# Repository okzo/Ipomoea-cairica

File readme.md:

# Ipomoea-cairica

60% JP or US Keyboard

このキーボードは組み立て時に日本語かUS配列を選択できます。

## JP

## US

## 組み立て方

[こちら](build_guide/build_guide.md)

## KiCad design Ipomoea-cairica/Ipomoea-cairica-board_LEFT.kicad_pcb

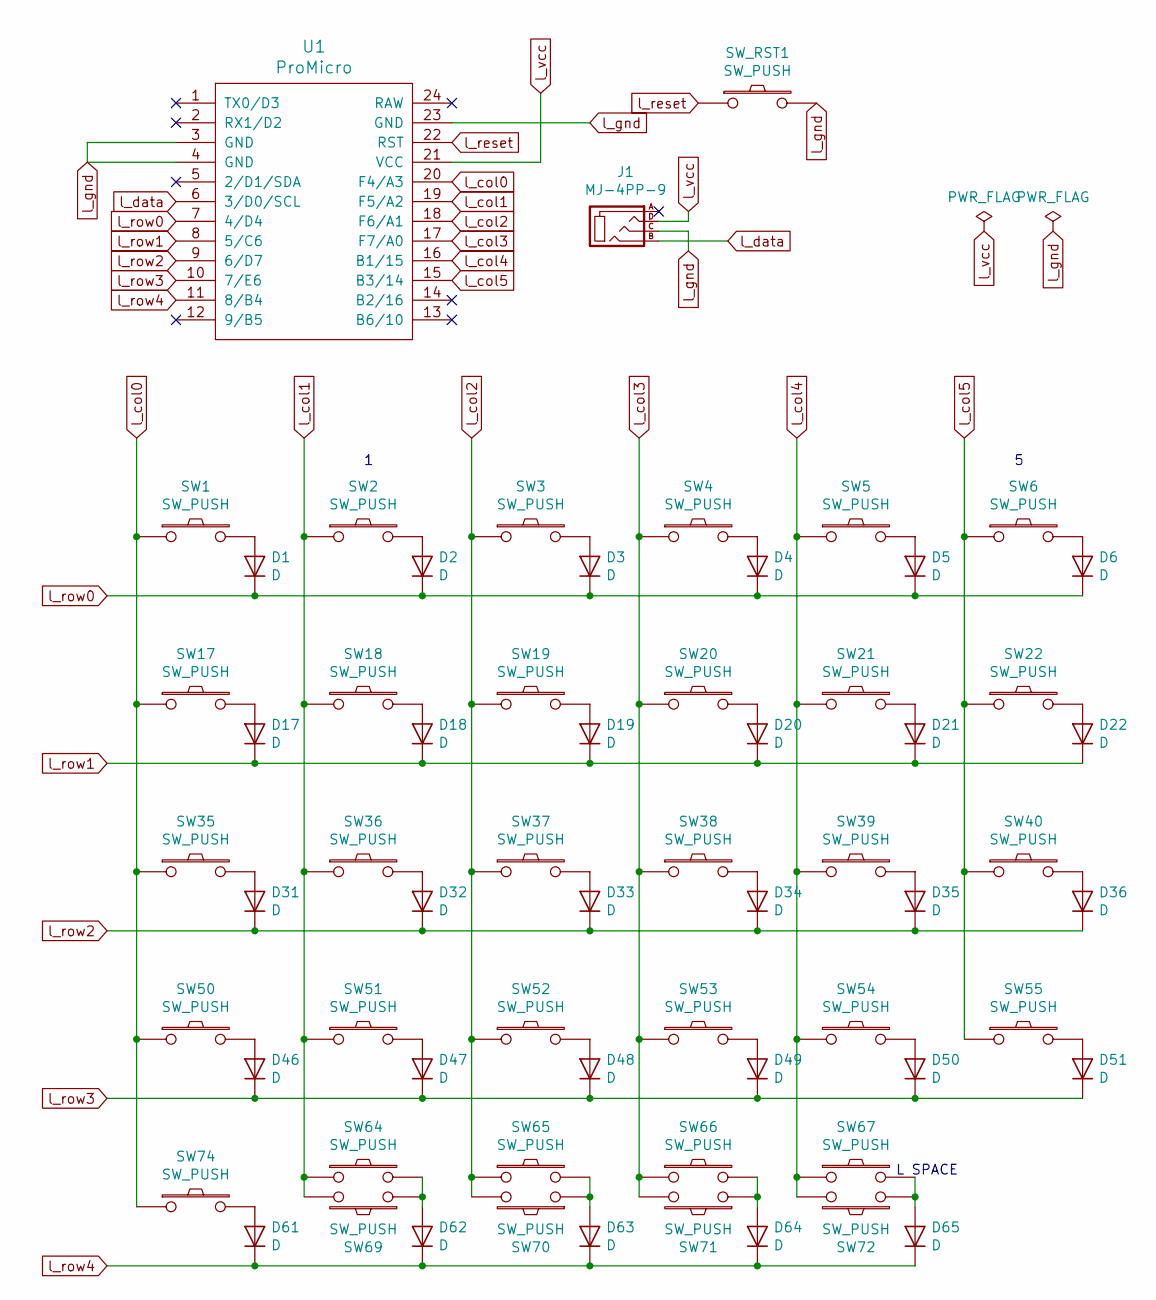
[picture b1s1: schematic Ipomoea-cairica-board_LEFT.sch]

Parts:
D1, D2, D3, D4, D5, D6, D17, D18, D19, D20, D21, D22, D31, D32, D33, D34, D35, D36, D46, D47, D48, D49, D50, D51, D61, D62, D63, D64, D65: D; D3_TH_SMD
J1: MJ-4PP-9; MJ-4PP-9_1side
SW1, SW2, SW3: SW_PUSH; CherryMX-Hotswap_1u_ProMicro
SW4: SW_PUSH; CherryMX-Hotswap_1u_TRRS
SW5, SW6, SW18, SW19, SW20, SW21, SW22, SW36, SW37, SW38, SW39, SW40, SW51, SW52, SW53, SW54, SW55, SW64, SW66: SW_PUSH; CherryMX-Hotswap_1u
SW17: SW_PUSH; CherryMX-Hotswap_1.5u
SW35, SW67: SW_PUSH; CherryMX-Hotswap_1.75u
SW50: SW_PUSH; CherryMX-Hotswap_2.25u
SW65, SW69, SW70, SW71, SW72, SW74: SW_PUSH; CherryMX-Hotswap_1.25u
SW_RST1: SW_PUSH; ResetSW_1side
U1: ProMicro

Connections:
unnamed: D1.2 (A), SW1.2
unnamed: D2.2 (A), SW2.2
unnamed: D3.2 (A), SW3.2
unnamed: D4.2 (A), SW4.2
unnamed: D5.2 (A), SW5.2
unnamed: D6.2 (A), SW6.2
unnamed: D17.2 (A), SW17.2
unnamed: D18.2 (A), SW18.2
unnamed: D19.2 (A), SW19.2
unnamed: D20.2 (A), SW20.2
unnamed: D21.2 (A), SW21.2
unnamed: D22.2 (A), SW22.2
unnamed: D31.2 (A), SW35.2
unnamed: D32.2 (A), SW36.2
unnamed: D33.2 (A), SW37.2
unnamed: D34.2 (A), SW38.2
unnamed: D35.2 (A), SW39.2
unnamed: D36.2 (A), SW40.2
unnamed: D46.2 (A), SW50.2
unnamed: D47.2 (A), SW51.2
unnamed: D48.2 (A), SW52.2
unnamed: D49.2 (A), SW53.2
unnamed: D50.2 (A), SW54.2
unnamed: D51.2 (A), SW55.2
unnamed: D61.2 (A), SW74.2
unnamed: D62.2 (A), SW64.2, SW69.1
unnamed: D63.2 (A), SW65.2, SW70.1
unnamed: D64.2 (A), SW66.2, SW71.1
unnamed: D65.2 (A), SW67.2, SW72.1
l_col0: SW1.1, SW17.1, SW35.1, SW50.1, SW74.1, U1.20 (F4/A3)
l_col1: SW2.1, SW18.1, SW36.1, SW51.1, SW64.1, SW69.2, U1.19 (F5/A2)
l_col2: SW3.1, SW19.1, SW37.1, SW52.1, SW65.1, SW70.2, U1.18 (F6/A1)
l_col3: SW4.1, SW20.1, SW38.1, SW53.1, SW66.1, SW71.2, U1.17 (F7/A0)
l_col4: SW5.1, SW21.1, SW39.1, SW54.1, SW67.1, SW72.2, U1.16 (B1/15)
l_col5: SW6.1, SW22.1, SW40.1, SW55.1, U1.15 (B3/14)
l_data: J1.B, U1.6 (3/D0/SCL)
l_gnd: J1.C, SW_RST1.2, U1.3 (GND), U1.4 (GND), U1.23 (GND)
l_reset: SW_RST1.1, U1.22 (RST)
l_row0: D1.1 (K), D2.1 (K), D3.1 (K), D4.1 (K), D5.1 (K), D6.1 (K), U1.7 (4/D4)
l_row1: D17.1 (K), D18.1 (K), D19.1 (K), D20.1 (K), D21.1 (K), D22.1 (K), U1.8 (5/C6)
l_row2: D31.1 (K), D32.1 (K), D33.1 (K), D34.1 (K), D35.1 (K), D36.1 (K), U1.9 (6/D7)
l_row3: D46.1 (K), D47.1 (K), D48.1 (K), D49.1 (K), D50.1 (K), D51.1 (K), U1.10 (7/E6)
l_row4: D61.1 (K), D62.1 (K), D63.1 (K), D64.1 (K), D65.1 (K), U1.11 (8/B4)
l_vcc: J1.D, U1.21 (VCC)

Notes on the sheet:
L SPACE

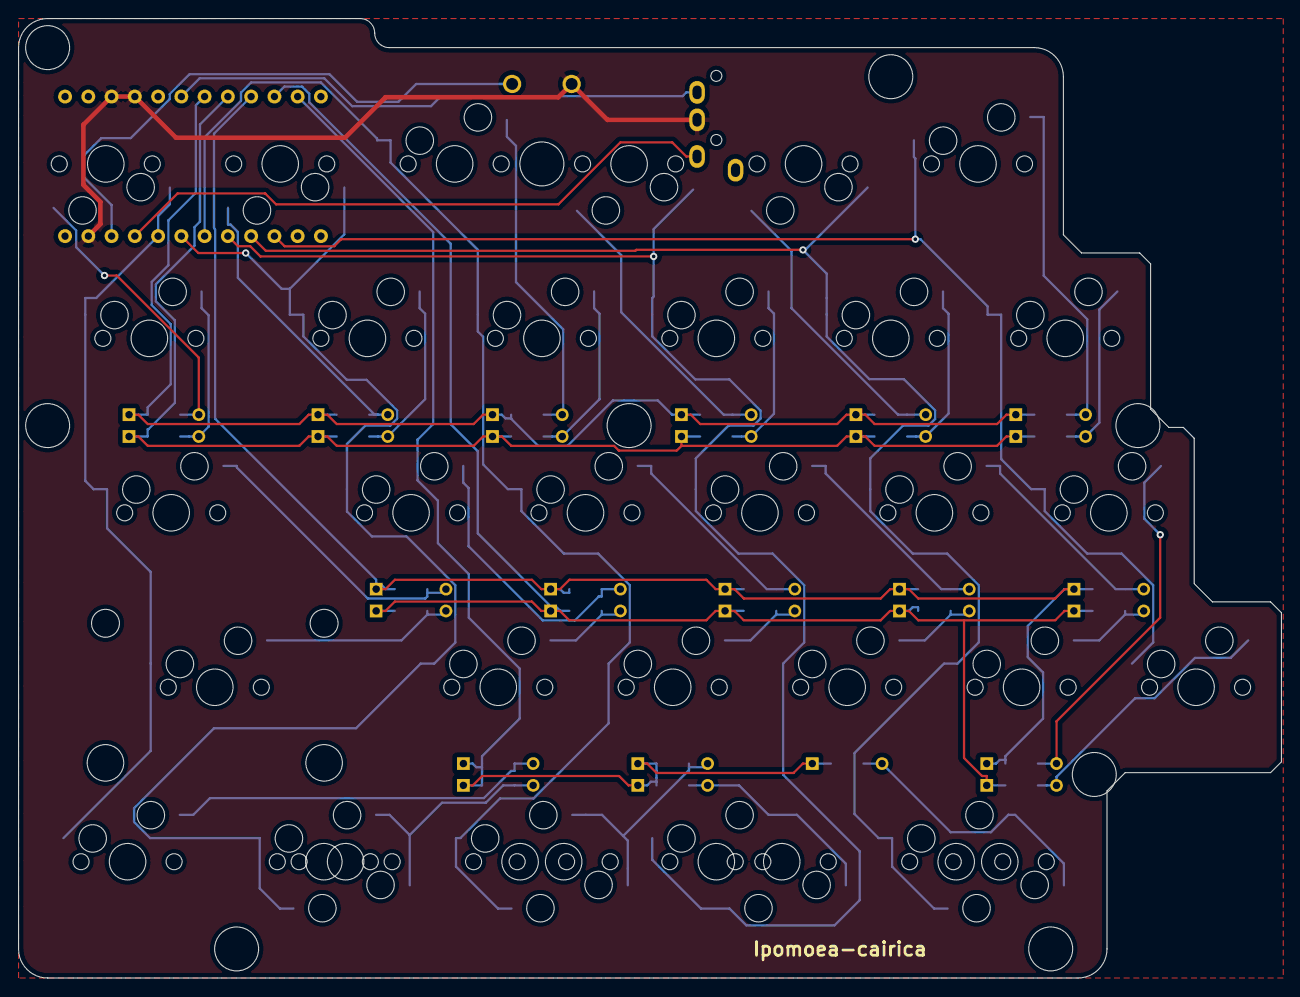
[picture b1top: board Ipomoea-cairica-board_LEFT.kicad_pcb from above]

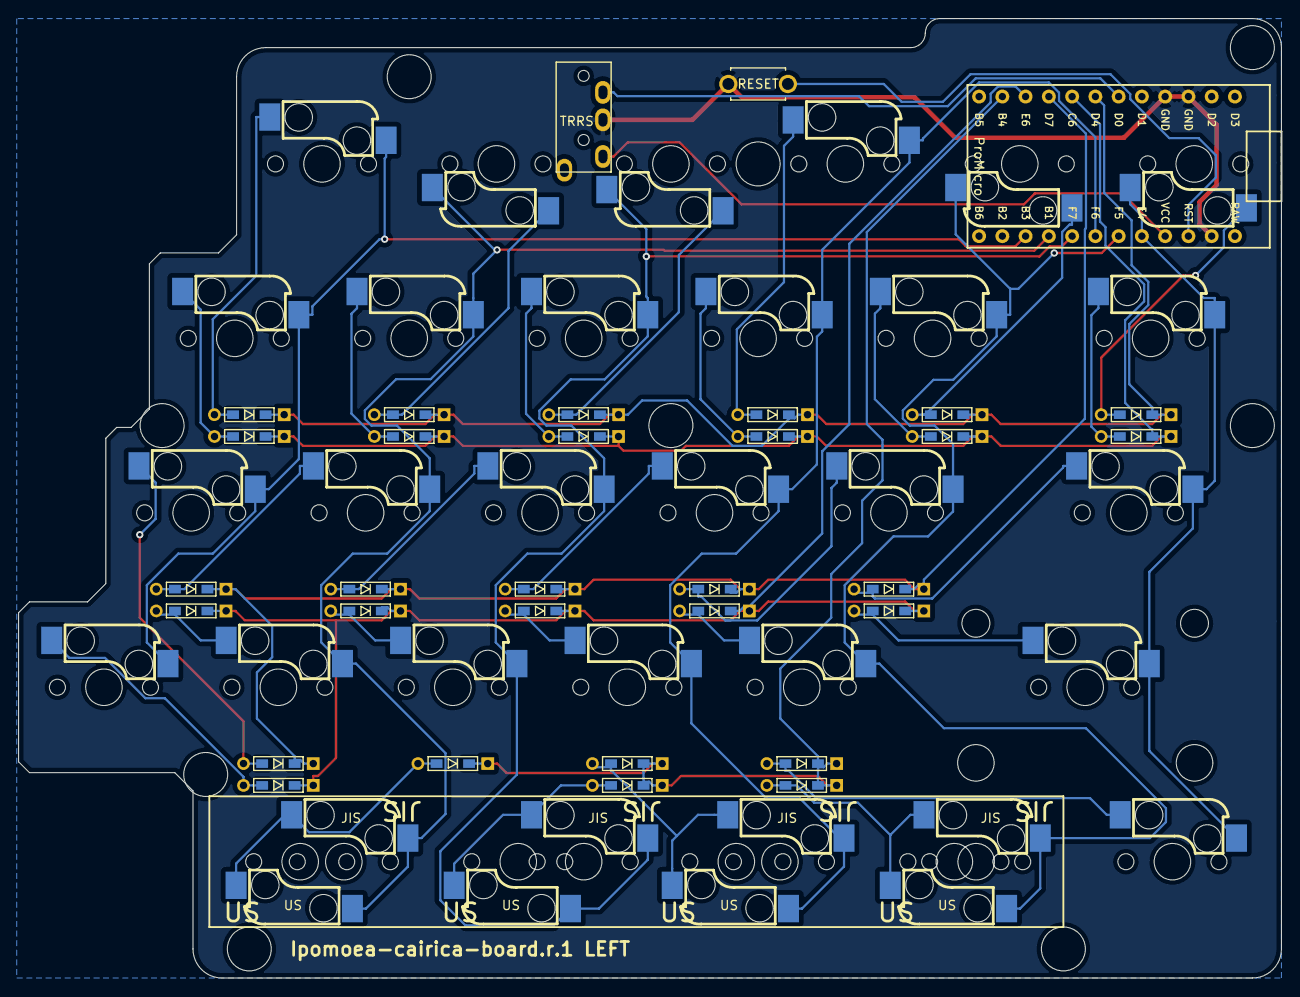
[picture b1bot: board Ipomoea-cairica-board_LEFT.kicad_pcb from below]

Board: 2 copper layers, 137.9 x 104.8 mm, 75 parts (2 on the bottom side), 44 nets.

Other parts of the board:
CUT_HOLE_CENTER: CUT_HOLE_CENTER_LEFT
M2_SPACER_HOLE_001, M2_SPACER_HOLE_005, M2_SPACER_HOLE_006, M2_SPACER_HOLE_008, M2_SPACER_HOLE_014, M2_SPACER_HOLE_015, M2_SPACER_HOLE_016, M2_SPACER_HOLE_018, M2_SPACER_HOLE_020: Val**; M2_SPACER_HOLE

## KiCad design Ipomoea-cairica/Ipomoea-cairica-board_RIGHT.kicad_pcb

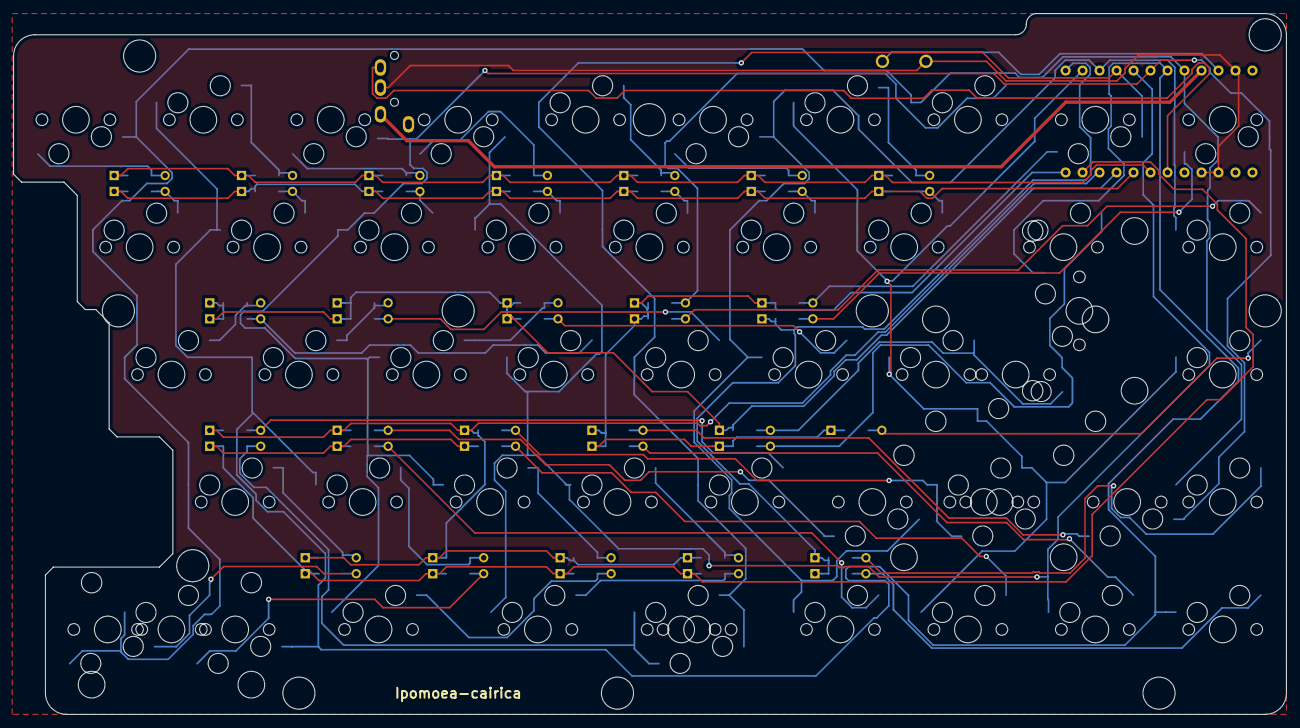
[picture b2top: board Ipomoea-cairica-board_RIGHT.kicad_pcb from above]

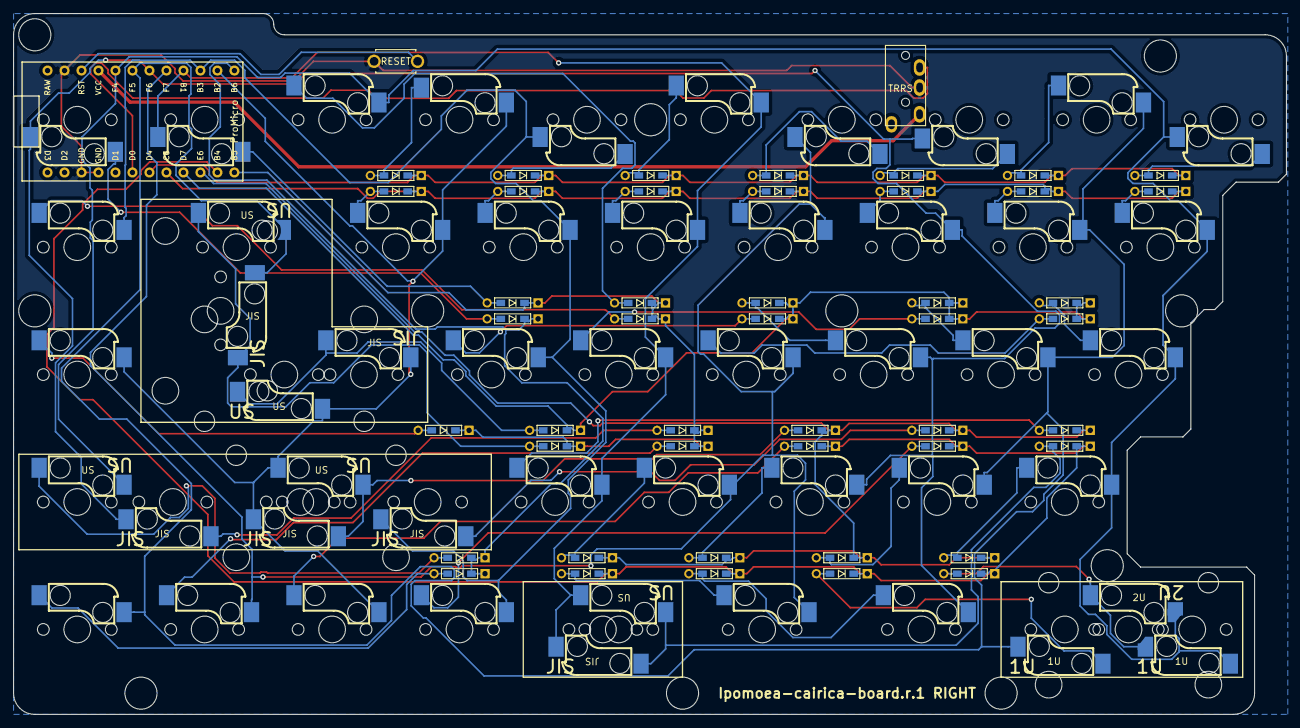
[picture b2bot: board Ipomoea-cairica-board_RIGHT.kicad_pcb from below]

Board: 2 copper layers, 190.3 x 104.8 mm, 110 parts (2 on the bottom side), 63 nets.

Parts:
CUT_HOLE_CENTER: CUT_HOLE_CENTER_RIGHT
D7, D8, D9, D10, D11, D12, D13, D14, D15, D16, D23, D24, D25, D26, D27, D28, D29, D30, D37, D38, D39, D40, D41, D42, D43, D44, D45, D52, D53, D54, D55, D56, D57, D58, D59, D60, D66, D67, D68, D69, D70, D71, D72, D73, D74: D; D3_TH_SMD
J2: MJ-4PP-9; MJ-4PP-9_1side
M2_SPACER_HOLE_002, M2_SPACER_HOLE_003, M2_SPACER_HOLE_004, M2_SPACER_HOLE_007, M2_SPACER_HOLE_009, M2_SPACER_HOLE_010, M2_SPACER_HOLE_011, M2_SPACER_HOLE_012, M2_SPACER_HOLE_013, M2_SPACER_HOLE_017, M2_SPACER_HOLE_019: Val**; M2_SPACER_HOLE
SW7, SW8, SW10, SW11, SW12, SW14, SW23, SW24, SW25, SW26, SW27, SW28, SW29, SW31, SW32, SW41, SW42, SW43, SW44, SW45, SW46, SW47, SW48, SW56, SW57, SW58, SW59, SW60, SW61, SW62, SW63, SW75, SW79, SW80, SW81, SW82, SW83: SW_PUSH; CherryMX-Hotswap_1u
SW9: SW_PUSH; CherryMX-Hotswap_1u_TRRS
SW13, SW15, SW16: SW_PUSH; CherryMX-Hotswap_1u_ProMicro
SW30: SW_PUSH; CherryMX-Hotswap_1.5u_BackSlash
SW33: SW_PUSH; CherryMX-Hotswap_2.25u
SW34: SW_PUSH; CherryMX-Hotswap_2u
SW49: SW_PUSH; CherryMX-Hotswap_2.75u
SW68: SW_PUSH; CherryMX-Hotswap_2u_RSFT
SW73: SW_PUSH; CherryMX-Hotswap_1u_RSFT_1
SW76, SW77, SW78: SW_PUSH; CherryMX-Hotswap_1.25u
SW_RST2: SW_PUSH; ResetSW_1side
U2: ProMicro

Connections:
unnamed: D7.2, SW7.2
unnamed: D8.2, SW8.2
unnamed: D9.2, SW9.2
unnamed: D10.2, SW10.2
unnamed: D11.2, SW11.2
unnamed: D12.2, SW12.2
unnamed: D13.2, SW13.2
unnamed: D14.2, SW14.2
unnamed: D15.2, SW15.2
unnamed: D16.2, SW16.2
unnamed: D23.2, SW23.2
unnamed: D24.2, SW24.2
unnamed: D25.2, SW25.2
unnamed: D26.2, SW26.2
unnamed: D27.2, SW27.2
unnamed: D28.2, SW28.2
unnamed: D29.2, SW29.2
unnamed: D30.2, SW31.2
unnamed: D37.2, SW41.2
unnamed: D38.2, SW42.2
unnamed: D39.2, SW43.2
unnamed: D40.2, SW44.2
unnamed: D41.2, SW45.2
unnamed: D42.2, SW46.2
unnamed: D43.2, SW32.2, SW33.1
unnamed: D44.2, SW30.2, SW34.1
unnamed: D45.2, SW47.2
unnamed: D52.2, SW56.2
unnamed: D53.2, SW57.2
unnamed: D54.2, SW58.2
unnamed: D55.2, SW59.2
unnamed: D56.2, SW60.2
unnamed: D57.2, SW61.2
unnamed: D58.2, SW48.2, SW49.1
unnamed: D59.2, SW62.2
unnamed: D60.2, SW63.2
unnamed: D66.2, SW68.2, SW73.1
unnamed: D67.2, SW75.2
unnamed: D68.2, SW76.2
unnamed: D69.2, SW77.2
unnamed: D70.2, SW78.2, SW83.1
unnamed: D71.2, SW79.2
unnamed: D72.2, SW80.2
unnamed: D73.2, SW81.2
unnamed: D74.2, SW82.2
r_col0: SW7.1, SW14.1, SW23.1, SW41.1, SW56.1, SW63.1, SW68.1, SW73.2, U2.20
r_col1: SW8.1, SW24.1, SW30.1, SW34.2, SW42.1, SW57.1, SW75.1, SW82.1, U2.19
r_col2: SW9.1, SW16.1, SW25.1, SW43.1, SW58.1, SW62.1, SW76.1, U2.18
r_col3: SW10.1, SW26.1, SW44.1, SW59.1, SW77.1, SW81.1, U2.17
r_col4: SW11.1, SW15.1, SW27.1, SW45.1, SW60.1, SW78.1, SW83.2, U2.16
r_col5: SW12.1, SW28.1, SW31.1, SW46.1, SW61.1, SW79.1, U2.15
r_col6: SW13.1, SW29.1, SW32.1, SW33.2, SW47.1, SW48.1, SW49.2, SW80.1, U2.14
r_data: J2.B, U2.6
r_gnd: J2.C, SW_RST2.2, U2.3, U2.4, U2.23
r_reset: SW_RST2.1, U2.22
r_row0: D7.1, D8.1, D9.1, D10.1, D11.1, D12.1, D13.1, U2.7
r_row1: D23.1, D24.1, D25.1, D26.1, D27.1, D28.1, D29.1, U2.8
r_row2: D37.1, D38.1, D39.1, D40.1, D41.1, D42.1, D43.1, U2.9
r_row3: D52.1, D53.1, D54.1, D55.1, D56.1, D57.1, D58.1, U2.10
r_row4: D66.1, D67.1, D68.1, D69.1, D70.1, D71.1, D72.1, U2.11
r_row5: D14.1, D15.1, D30.1, D44.1, D45.1, D59.1, D73.1, U2.12
r_row6: D16.1, D60.1, D74.1, U2.13
r_vcc: J2.D, U2.21

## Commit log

2020-03-29 add projects
